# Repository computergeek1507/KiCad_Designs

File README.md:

# Copyright and Disclaimer
Copyright: Scott Hanson

This documentation describes Open Hardware and is licensed under the CERN OHL v. 1.2.

You may redistribute and modify this documentation under the terms of the CERN OHL v.1.2. (http://ohwr.org/cernohl). This documentation is distributed WITHOUT ANY EXPRESS OR IMPLIED WARRANTY, INCLUDING OF MERCHANTABILITY, SATISFACTORY QUALITY AND FITNESS FOR A PARTICULAR PURPOSE. Please see the CERN OHL v.1.2 for applicable conditions

# KiCad Designs
Repo for all my OSH KiCad PCB Designs

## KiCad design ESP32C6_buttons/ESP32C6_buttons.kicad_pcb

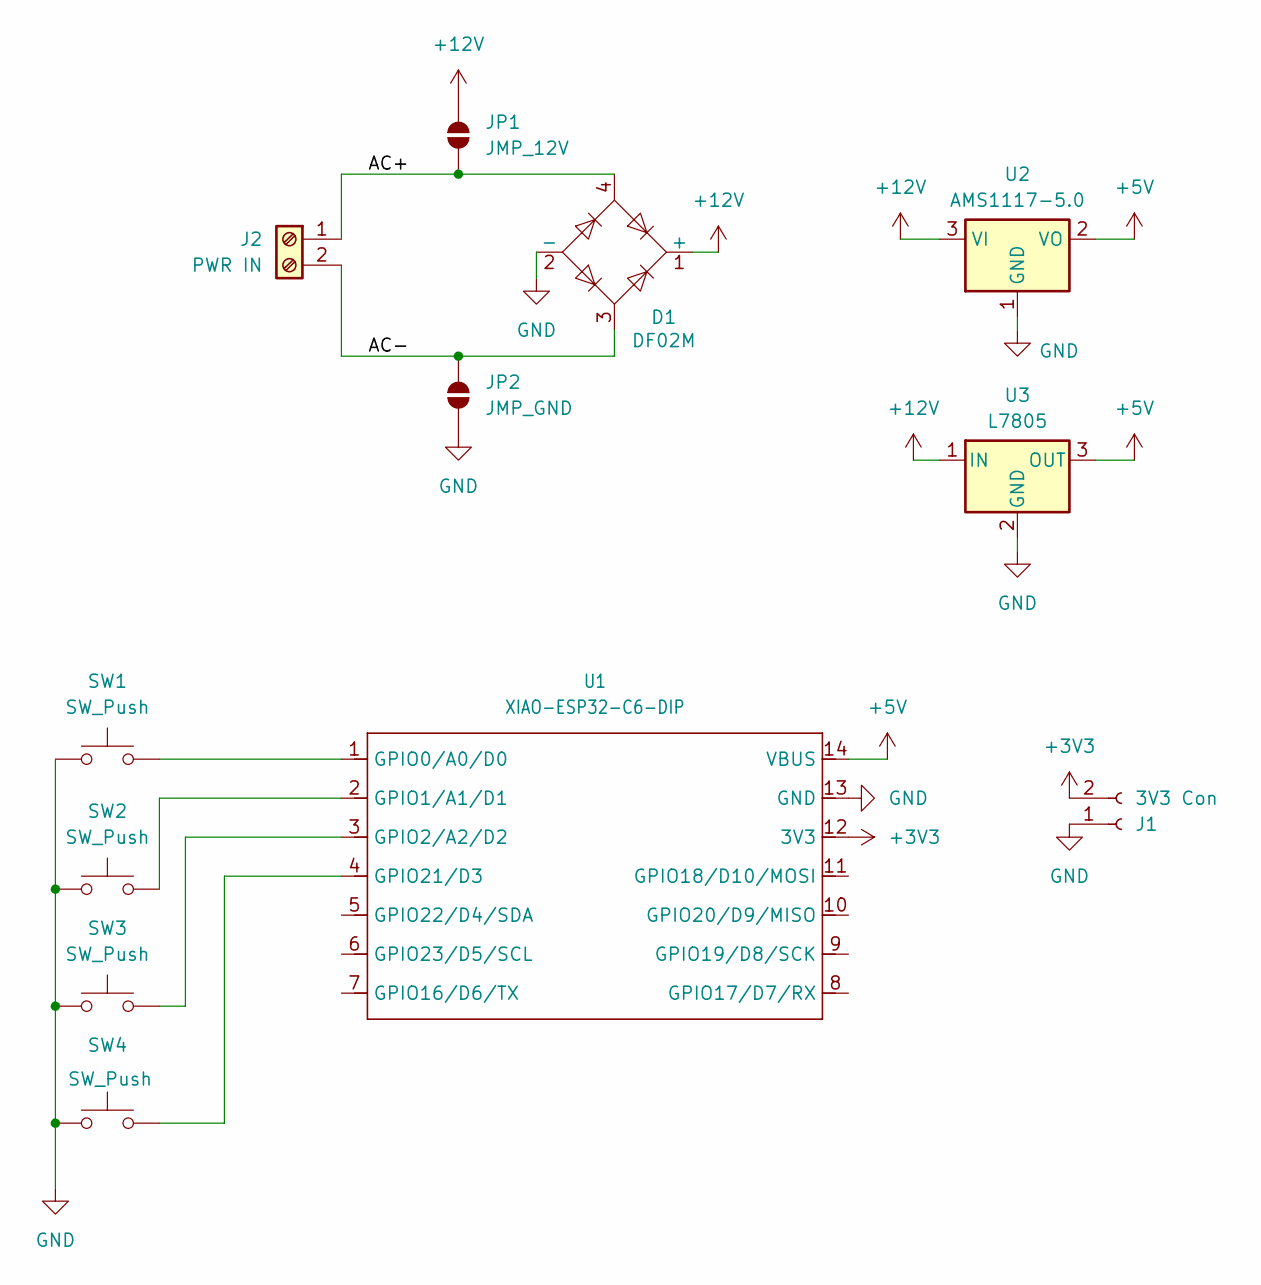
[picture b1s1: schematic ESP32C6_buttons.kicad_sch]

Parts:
D1: DF02M; Diode_Bridge_DIP-4_W7.62mm_P5.08mm
J1: 3V3 Con; JST_XH_B2B-XH-A_1x02_P2.50mm_Vertical
J2: PWR IN; PhoenixContact_MCV_1,5_2-G-5.08_1x02_P5.08mm_Vertical
JP1: JMP_12V; SolderJumper-2_P1.3mm_Open_Pad1.0x1.5mm
JP2: JMP_GND; SolderJumper-2_P1.3mm_Open_Pad1.0x1.5mm
SW1, SW2, SW3, SW4: SW_Push; SW_PUSH_6mm
U1: XIAO-ESP32-C6-DIP
U2: AMS1117-5.0; SOT-223-3_TabPin2
U3: L7805; OKI-78SR_Horz

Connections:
+3V3: J1.2, U1.12 (3V3)
+5V: U1.14 (VBUS), U2.2 (VO), U3.3 (OUT)
+12V: D1.1 (+), JP1.2 (B), U2.3 (VI), U3.1 (IN)
/AC+: D1.4, J2.1, JP1.1 (A)
/AC-: D1.3, J2.2, JP2.2 (B)
GND: D1.2 (-), J1.1, JP2.1 (A), SW1.1, SW2.1, SW3.1, SW4.1, U1.13 (GND), U2.1 (GND), U3.2 (GND)
unnamed: SW1.2, U1.1 (GPIO0/A0/D0)
unnamed: SW2.2, U1.2 (GPIO1/A1/D1)
unnamed: SW3.2, U1.3 (GPIO2/A2/D2)
unnamed: SW4.2, U1.4 (GPIO21/D3)

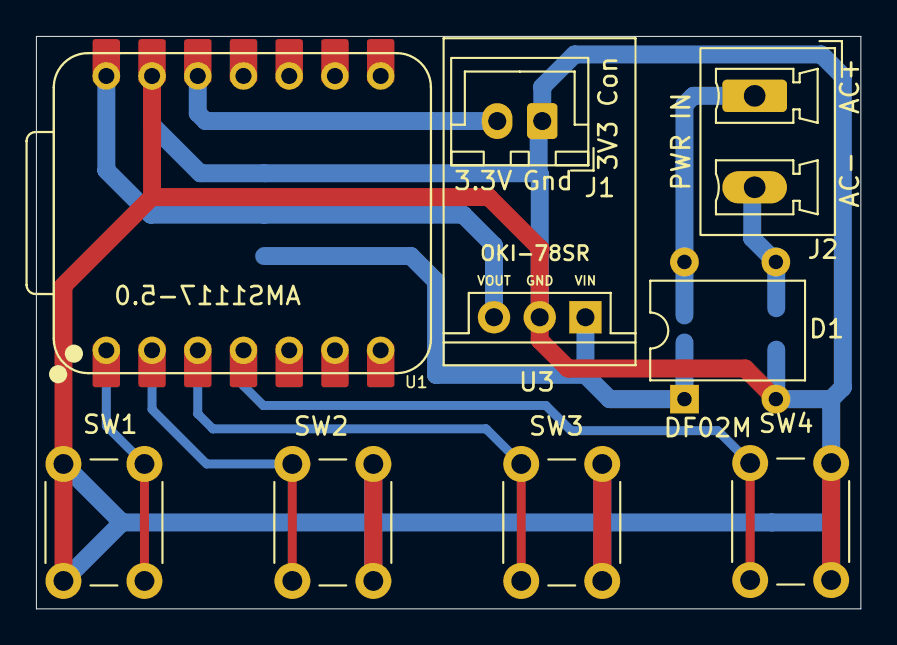
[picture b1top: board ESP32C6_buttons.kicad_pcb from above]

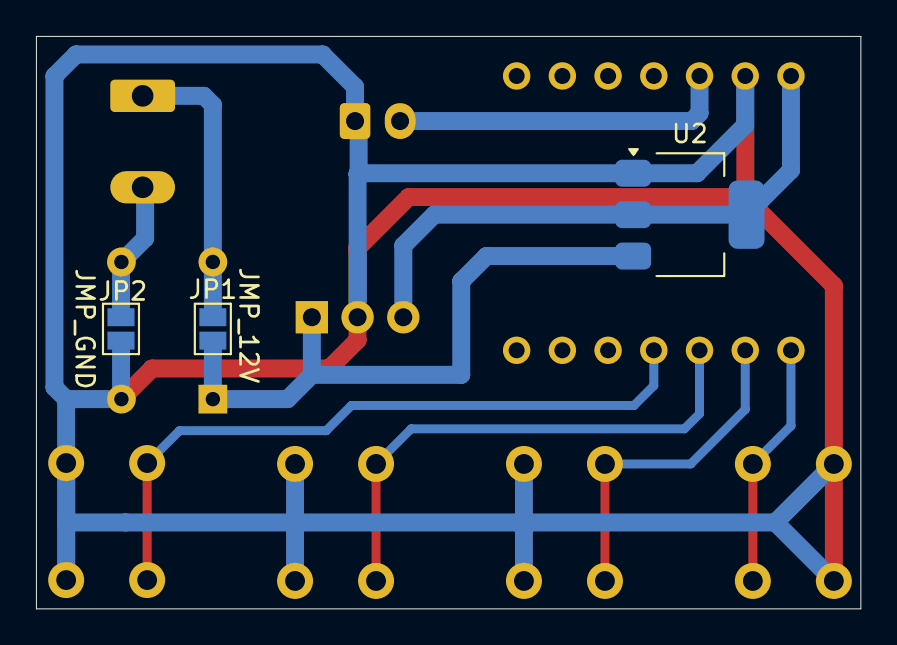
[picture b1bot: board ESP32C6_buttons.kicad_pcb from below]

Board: 2 copper layers, 45.8 x 31.8 mm, 12 parts (3 on the bottom side), 10 nets.

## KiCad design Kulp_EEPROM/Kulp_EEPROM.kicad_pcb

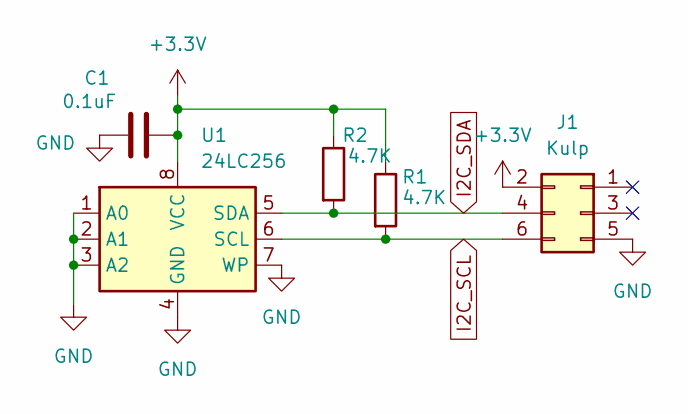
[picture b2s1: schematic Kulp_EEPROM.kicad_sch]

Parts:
C1: 0.1uF; C_0603_1608Metric_Pad1.08x0.95mm_HandSolder; MPN CL10B104KB8NNWC; LCSC C14663
J1: Kulp; 2x03_Horizontal_SMD; MPN PPTC032LFBN-RC; Digi-Key_PN S7071-ND
R1, R2: 4.7K; R_0603_1608Metric_Pad0.98x0.95mm_HandSolder; MPN RC0603JR-074K7L; LCSC C23162
U1: 24LC256; SOIC-8_3.9x4.9mm_P1.27mm; MPN 24LC256T-I/SN; Digi-Key_PN 24LC256T-I/SNCT-ND

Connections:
+3.3V: C1.1, J1.2, R1.1, R2.1, U1.8 (VCC)
GND: C1.2, J1.5, U1.1 (A0), U1.2 (A1), U1.3 (A2), U1.4 (GND), U1.7 (WP)
I2C_SCL: J1.6, R1.2, U1.6 (SCL)
I2C_SDA: J1.4, R2.2, U1.5 (SDA)

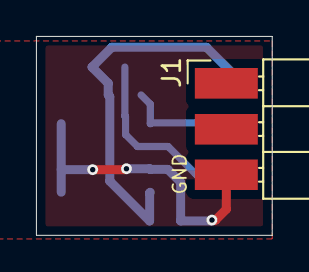
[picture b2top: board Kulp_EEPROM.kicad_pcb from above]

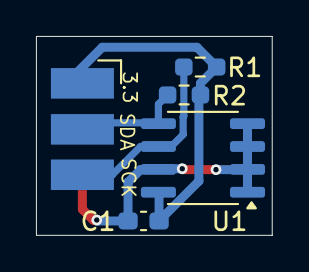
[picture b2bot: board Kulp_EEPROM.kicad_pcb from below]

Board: 2 copper layers, 13.1 x 11.0 mm, 5 parts (4 on the bottom side), 4 nets.

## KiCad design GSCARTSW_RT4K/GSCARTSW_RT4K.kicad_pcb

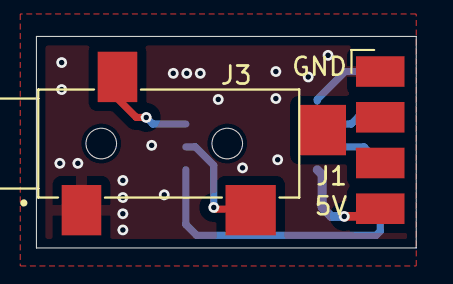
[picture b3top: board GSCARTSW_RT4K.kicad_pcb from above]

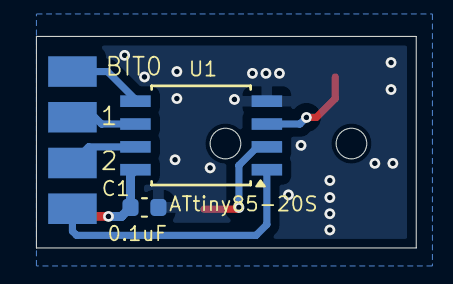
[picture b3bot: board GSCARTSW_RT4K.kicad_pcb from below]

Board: 2 copper layers, 21.1 x 11.8 mm, 4 parts (2 on the bottom side), 8 nets.

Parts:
C1: 0.1uF; C_0603_1608Metric
J1: Conn_02x04_Top_Bottom; PinSocket_2x04_P2.54mm_Horizontal_SMD
J3: SJ-3524-SMT-PI; CUI_SJ-3524-SMT-PI
U1: ATtiny85-20S; SOIC-8W_5.3x5.3mm_P1.27mm

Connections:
+5V: C1.1, J1.4, U1.8 (VCC)
GND: C1.2, J1.1, J3.1, U1.4 (GND)
IN_BIT0: J1.5, U1.5 (AREF/PB0)
IN_BIT1: J1.6, U1.6 (PB1)
IN_BIT2: J1.7, U1.7 (PB2)
RESET: J1.8, U1.1 (~RESET/PB5)
RX: J3.3, U1.3 (XTAL2/PB4)
TX: J3.2, U1.2 (XTAL1/PB3)

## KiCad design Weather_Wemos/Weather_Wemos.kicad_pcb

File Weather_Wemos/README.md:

# Copyright and Disclaimer
Copyright: Scott Hanson

This documentation describes Open Hardware and is licensed under the CERN OHL v. 1.2.

You may redistribute and modify this documentation under the terms of the CERN OHL v.1.2. (http://ohwr.org/cernohl). This documentation is distributed WITHOUT ANY EXPRESS OR IMPLIED WARRANTY, INCLUDING OF MERCHANTABILITY, SATISFACTORY QUALITY AND FITNESS FOR A PARTICULAR PURPOSE. Please see the CERN OHL v.1.2 for applicable conditions

# Weather Wemos

Breakout board for the Wemos D1 Mini to use it with the [Sparkfun Weather Meter Kit](https://www.sparkfun.com/products/15901). The design was made with all through hole components for easy assembly by most users. Open source applications were used to create this controller. [KiCad](http://kicad-pcb.org/) was used for the PCB design, and [LibreOffice](https://www.libreoffice.org/) for the documentation.

To order your own PCB upload the gerber.zip file to your favorite PCB manufacture of choice, I personally use [jlcpcb.com](https://jlcpcb.com/).

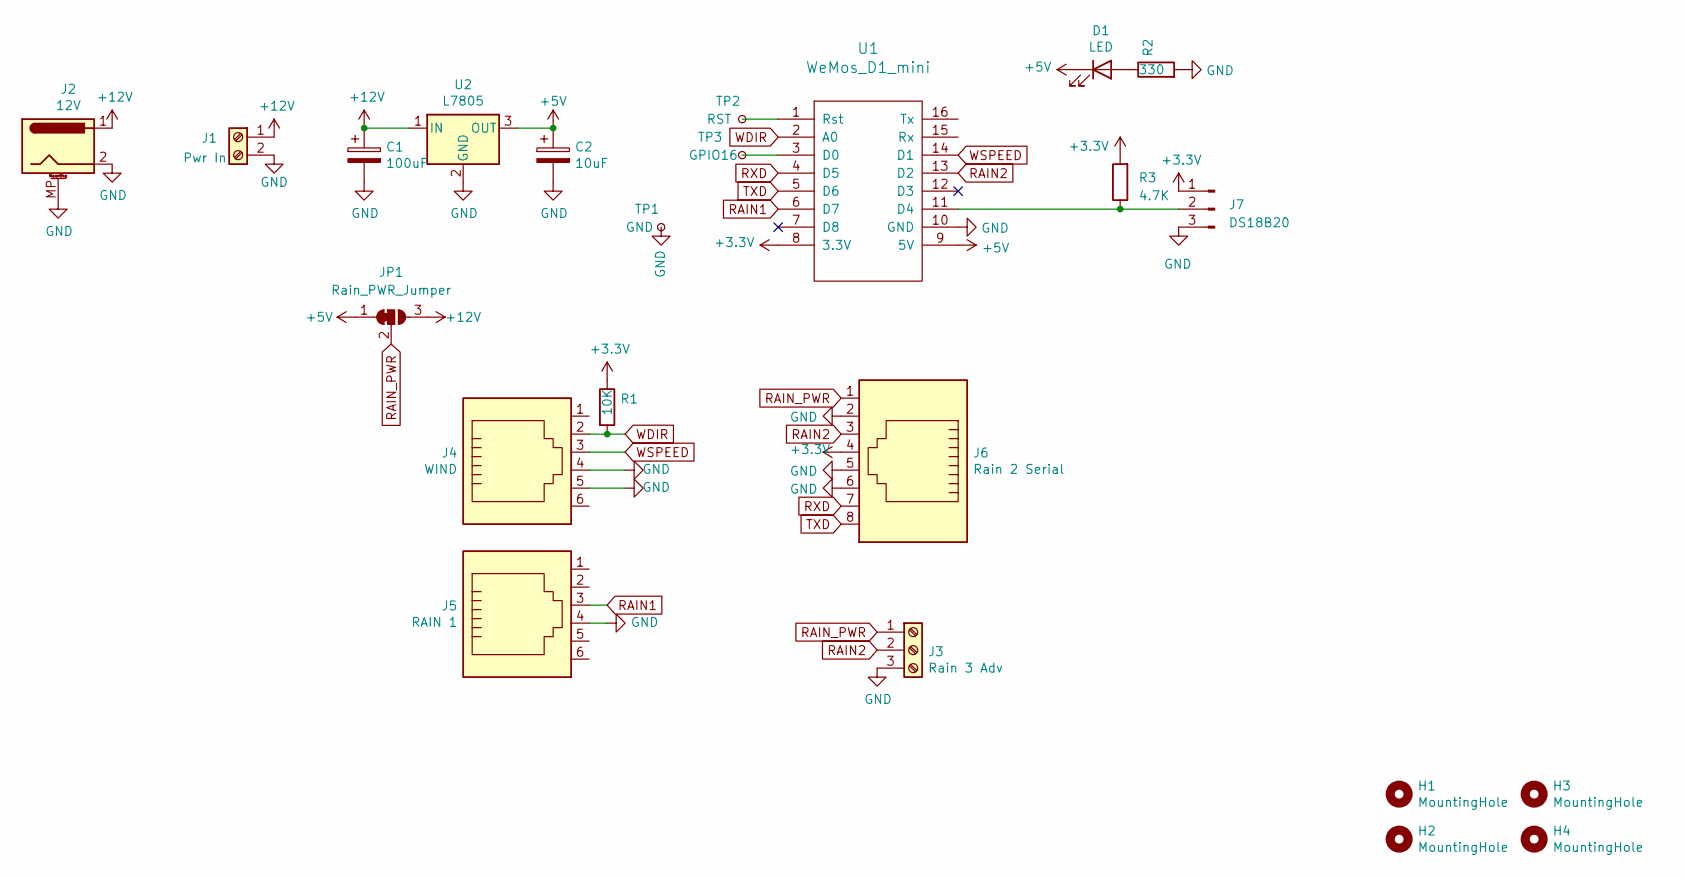
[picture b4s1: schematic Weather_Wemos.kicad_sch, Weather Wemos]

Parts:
C1: 100uF; CP_Radial_D5.0mm_P2.50mm
C2: 10uF; CP_Radial_D5.0mm_P2.50mm
D1: LED; LED_D3.0mm
H1, H2, H3, H4: MountingHole; MountingHole_3.7mm
J1: Pwr In; TerminalBlock_Phoenix_MKDS-1,5-2_1x02_P5.00mm_Horizontal
J2: 12V; BarrelJack_Horizontal
J3: Rain 3 Adv; TerminalBlock_Phoenix_MKDS-1,5-3_1x03_P5.00mm_Horizontal
J4: WIND; RJ12_Amphenol_54601; Digikey AE10391-ND
J5: RAIN 1; RJ12_Amphenol_54601; Digikey AE10391-ND
J6: Rain 2 Serial; RJ45_Amphenol_54602-x08_Horizontal
J7: DS18B20; JST_XH_B3B-XH-A_1x03_P2.50mm_Vertical
JP1: Rain_PWR_Jumper; SolderJumper-3_P1.3mm_Bridged2Bar12_RoundedPad1.0x1.5mm_Num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
R1: 10K; R_Axial_DIN0207_L6.3mm_D2.5mm_P7.62mm_Horizontal
R2: 330; R_Axial_DIN0207_L6.3mm_D2.5mm_P7.62mm_Horizontal
R3: 4.7K; R_Axial_DIN0207_L6.3mm_D2.5mm_P7.62mm_Horizontal
TP1: GND; TestPoint_Pad_1.5x1.5mm
TP2: RST; TestPoint_Pad_1.5x1.5mm
TP3: GPIO16; TestPoint_Pad_1.5x1.5mm
U1: WeMos_D1_mini; wemos-d1-mini-connectors-only
U2: L7805; TO-220-3_Vertical

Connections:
+3V3: J6.4, J7.1, R1.1, R3.2, U1.8 (3.3V)
+5V: C2.1, D1.1 (K), JP1.1 (A), U1.9 (5V), U2.3 (OUT)
+12V: C1.1, J1.1, J2.1, JP1.3 (B), U2.1 (IN)
GND: C1.2, C2.2, J1.2, J2.2, J2.MP (MountPin), J3.3, J4.4, J4.5, J5.4, J6.2, J6.5, J6.6, J7.3, R2.2, TP1.1, U1.10 (GND), U2.2 (GND)
unnamed: D1.2 (A), R2.1
unnamed: J7.2, R3.1, U1.11 (D4)
unnamed: TP3.1, U1.3 (D0)
unnamed: TP2.1, U1.1 (Rst)
RAIN1: J5.3, U1.6 (D7)
RAIN2: J3.2, J6.3, U1.13 (D2)
RAIN_PWR: J3.1, J6.1, JP1.2 (C)
RXD: J6.7, U1.4 (D5)
TXD: J6.8, U1.5 (D6)
WDIR: J4.2, R1.2, U1.2 (A0)
WSPEED: J4.3, U1.14 (D1)

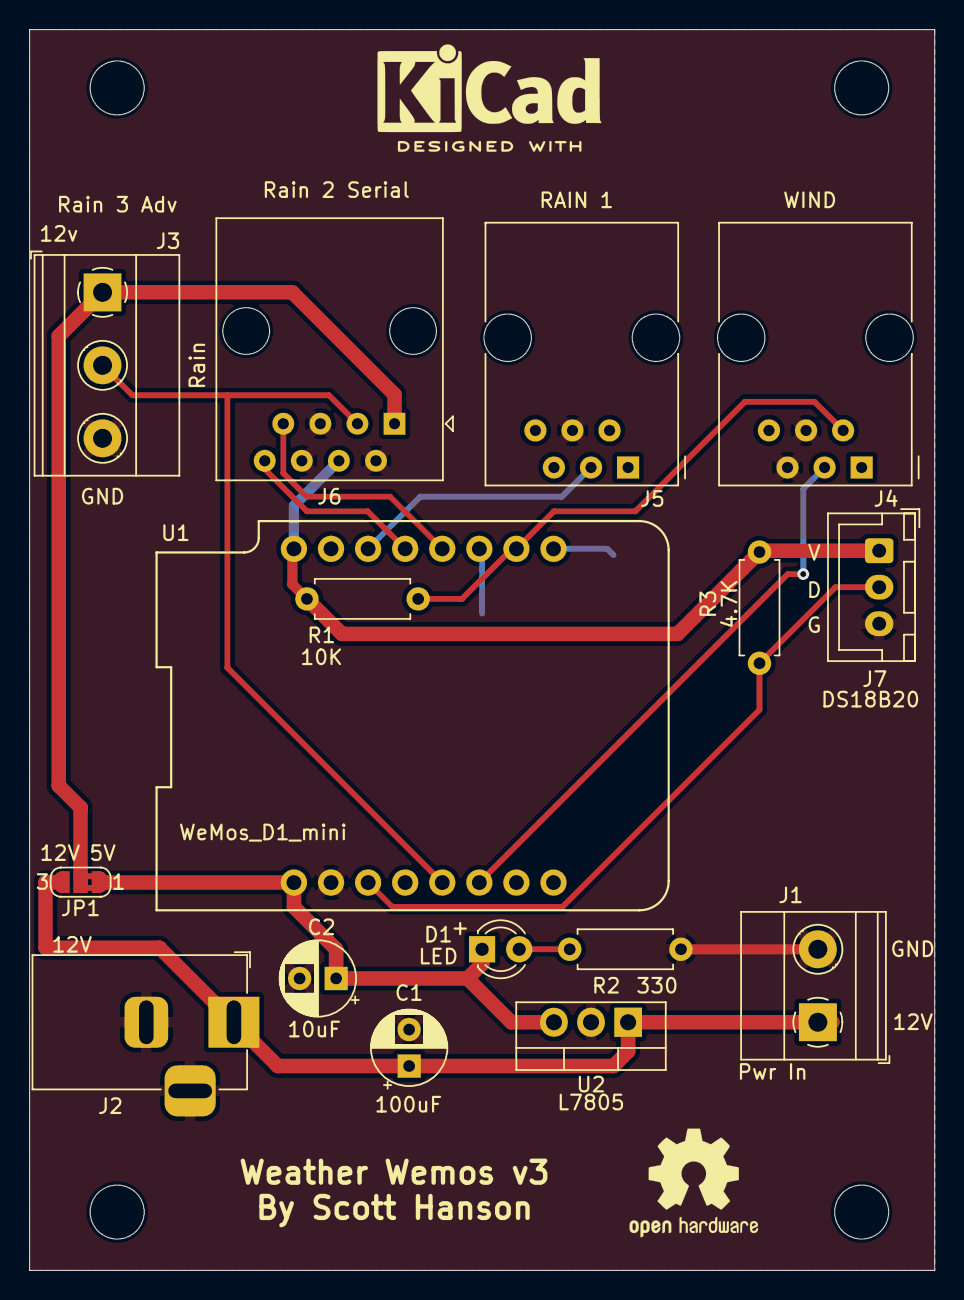
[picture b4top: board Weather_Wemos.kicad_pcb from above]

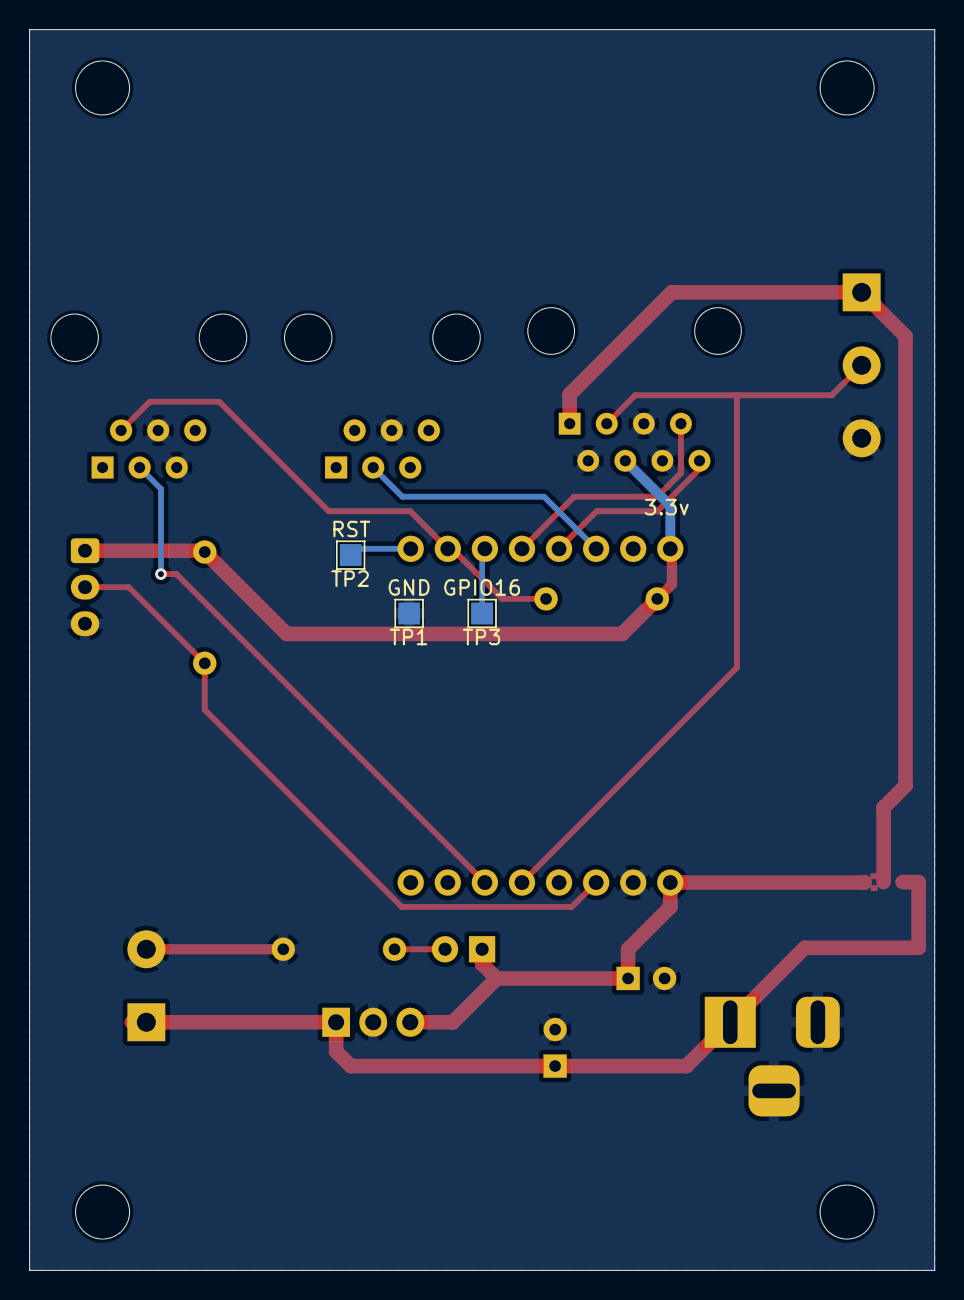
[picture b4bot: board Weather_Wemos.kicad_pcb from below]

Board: 2 copper layers, 62.0 x 85.0 mm, 23 parts (3 on the bottom side), 15 nets.

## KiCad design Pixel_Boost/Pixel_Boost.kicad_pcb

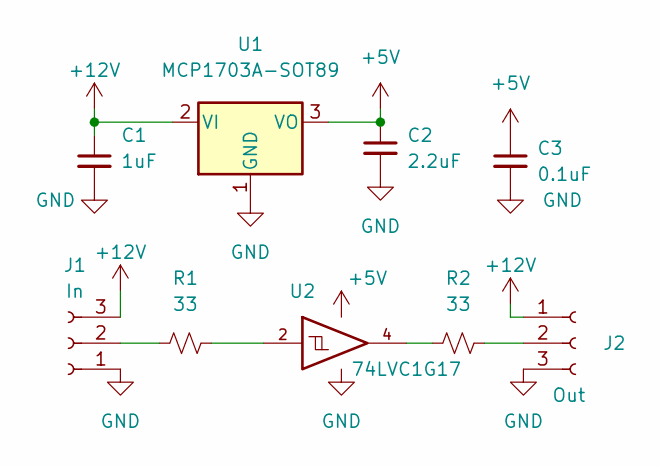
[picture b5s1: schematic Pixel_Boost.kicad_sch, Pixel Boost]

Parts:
C1: 1uF; R_0603_1608Metric; LCSC C15849
C2: 2.2uF; R_0603_1608Metric; LCSC C23630
C3: 0.1uF; R_0603_1608Metric; LCSC C14663
J1: In; PhoenixContact_MCV_1,5_3-G-3.81_1x03_P3.81mm_Vertical
J2: Out; PhoenixContact_MCV_1,5_3-G-3.81_1x03_P3.81mm_Vertical
R1, R2: 33; R_0603_1608Metric; LCSC C4184
U1: MCP1703A-SOT89; SOT-89-3; LCSC C16106
U2: 74LVC1G17; SOT-23-5; LCSC C7836

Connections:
+5V: C2.1, C3.1, U1.3 (VO), U2.5 (VCC)
+12V: C1.1, J1.3, J2.1, U1.2 (VI)
GND: C1.2, C2.2, C3.2, J1.1, J2.3, U1.1 (GND), U2.3 (GND)
unnamed: J1.2, R1.1
unnamed: J2.2, R2.2
unnamed: R1.2, U2.2
unnamed: R2.1, U2.4

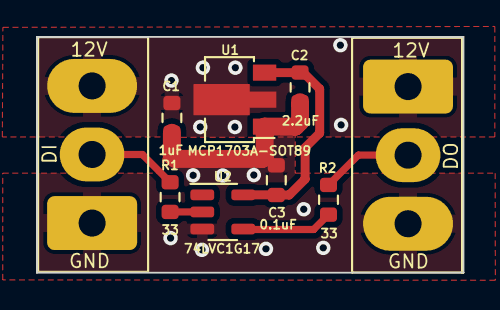
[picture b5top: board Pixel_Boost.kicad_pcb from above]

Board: 2 copper layers, 23.7 x 13.1 mm, 9 parts (0 on the bottom side), 7 nets.

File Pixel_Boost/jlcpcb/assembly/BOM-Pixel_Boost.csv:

Comment,Designator,Footprint,LCSC
0.1uF,C3,R_0603_1608Metric,C14663
1uF,C1,R_0603_1608Metric,C15849
MCP1703A,U1,SOT-89-3,C16106
2.2uF,C2,R_0603_1608Metric,C23630
33,"R1,R2",R_0603_1608Metric,C4184
74LVC1G17,U2,SOT-23-5,C840096
Out,J2,"PhoenixContact_MCV_1,5_3-G-3.81_1x03_P3.81mm_Vertical",
In,J1,"PhoenixContact_MCV_1,5_3-G-3.81_1x03_P3.81mm_Vertical",

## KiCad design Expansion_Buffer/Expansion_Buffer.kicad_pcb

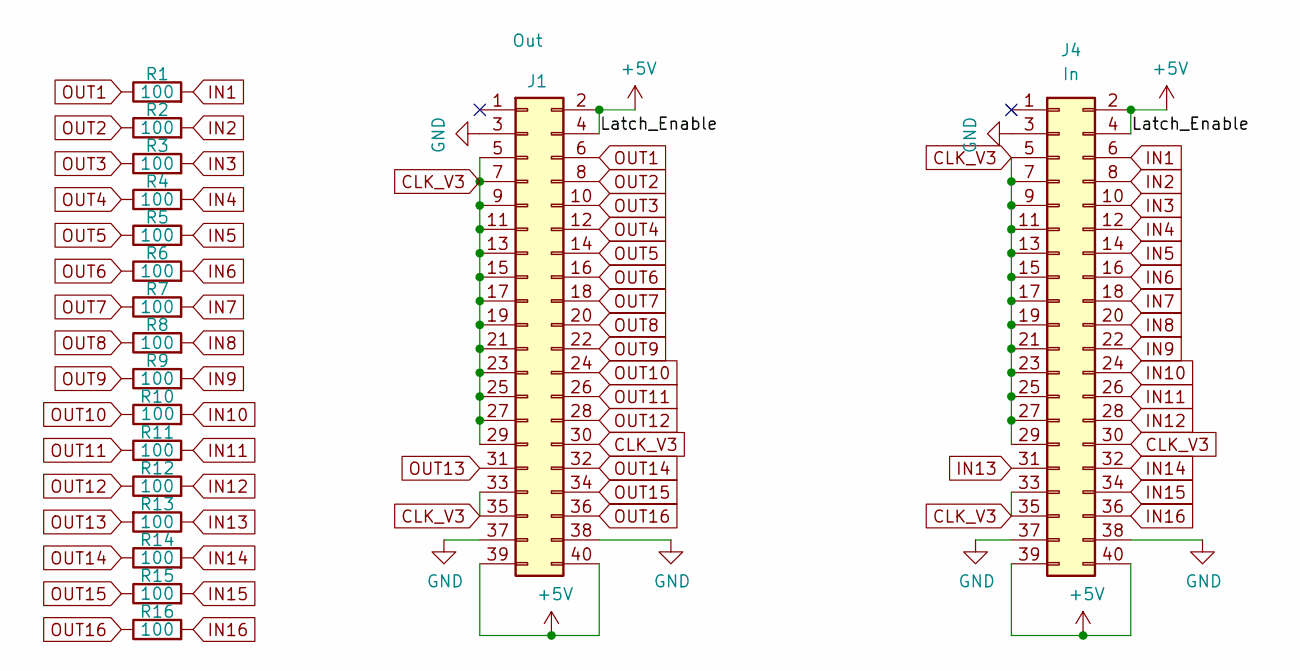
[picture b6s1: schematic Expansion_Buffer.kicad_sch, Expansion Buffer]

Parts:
J1: Out; PinSocket_2x20_P2.54mm_Vertical; MPN SBH11-PBPC-D20-ST-BK; Digi-Key_PN S9175-ND
J4: In; IDC-Header_2x20_P2.54mm_Vertical; MPN SBH11-PBPC-D20-ST-BK; Digi-Key_PN S9175-ND
R1, R2, R3, R4, R5, R6, R7, R8, R9, R10, R11, R12, R13, R14, R15, R16: 100; R_0805_2012Metric_Pad1.20x1.40mm_HandSolder

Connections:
+5V: J1.2, J1.4, J1.39, J1.40; also elsewhere on the board
CLK_V3: J1.5, J1.7, J1.9, J1.11, J1.13, J1.15, J1.17, J1.19, J1.21, J1.23, J1.25, J1.27, J1.29, J1.30, J1.33, J1.35; also elsewhere on the board
GND: J1.3, J1.37, J1.38; also elsewhere on the board
IN1: R1.2; also elsewhere on the board
IN2: R2.2; also elsewhere on the board
IN3: R3.2; also elsewhere on the board
IN4: R4.2; also elsewhere on the board
IN5: R5.2; also elsewhere on the board
IN6: R6.2; also elsewhere on the board
IN7: R7.2; also elsewhere on the board
IN8: R8.2; also elsewhere on the board
IN9: R9.2; also elsewhere on the board
IN10: R10.2; also elsewhere on the board
IN11: R11.2; also elsewhere on the board
IN12: R12.2; also elsewhere on the board
IN13: R13.1; also elsewhere on the board
IN14: R14.2; also elsewhere on the board
IN15: R15.2; also elsewhere on the board
IN16: R16.2; also elsewhere on the board
OUT1: J1.6, R1.1
OUT2: J1.8, R2.1
OUT3: J1.10, R3.1
OUT4: J1.12, R4.1
OUT5: J1.14, R5.1
OUT6: J1.16, R6.1
OUT7: J1.18, R7.1
OUT8: J1.20, R8.1
OUT9: J1.22, R9.1
OUT10: J1.24, R10.1
OUT11: J1.26, R11.1
OUT12: J1.28, R12.1
OUT13: J1.31, R13.2
OUT14: J1.32, R14.1
OUT15: J1.34, R15.1
OUT16: J1.36, R16.1

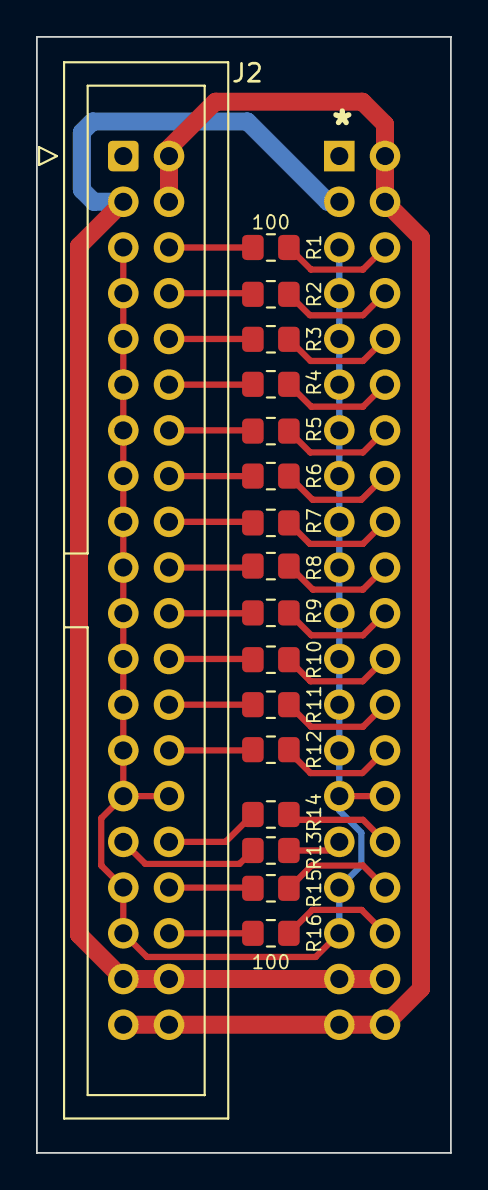
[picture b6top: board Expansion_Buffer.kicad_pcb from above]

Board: 2 copper layers, 23.0 x 62.0 mm, 18 parts (1 on the bottom side), 35 nets.

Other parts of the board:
J2: In; IDC-Header_2x20_P2.54mm_Vertical

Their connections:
+5V: J2.2, J2.4, J2.39, J2.40; also elsewhere on the board
CLK_V3: J2.5, J2.7, J2.9, J2.11, J2.13, J2.15, J2.17, J2.19, J2.21, J2.23, J2.25, J2.27, J2.29, J2.30, J2.33, J2.35; also elsewhere on the board
GND: J2.3, J2.37, J2.38; also elsewhere on the board
IN1: J2.6; also elsewhere on the board
IN2: J2.8; also elsewhere on the board
IN3: J2.10; also elsewhere on the board
IN4: J2.12; also elsewhere on the board
IN5: J2.14; also elsewhere on the board
IN6: J2.16; also elsewhere on the board
IN7: J2.18; also elsewhere on the board
IN8: J2.20; also elsewhere on the board
IN9: J2.22; also elsewhere on the board
IN10: J2.24; also elsewhere on the board
IN11: J2.26; also elsewhere on the board
IN12: J2.28; also elsewhere on the board
IN13: J2.31; also elsewhere on the board
IN14: J2.32; also elsewhere on the board
IN15: J2.34; also elsewhere on the board
IN16: J2.36; also elsewhere on the board

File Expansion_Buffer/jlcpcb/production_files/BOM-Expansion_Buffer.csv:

Comment,Designator,Footprint,LCSC
100,"R1,R10,R11,R12,R13,R14,R15,R16,R2,R3,R4,R5,R6,R7,R8,R9",R_0805_2012Metric_Pad1.20x1.40mm_HandSolder,C17408
In,J2,IDC-Header_2x20_P2.54mm_Vertical,C9138

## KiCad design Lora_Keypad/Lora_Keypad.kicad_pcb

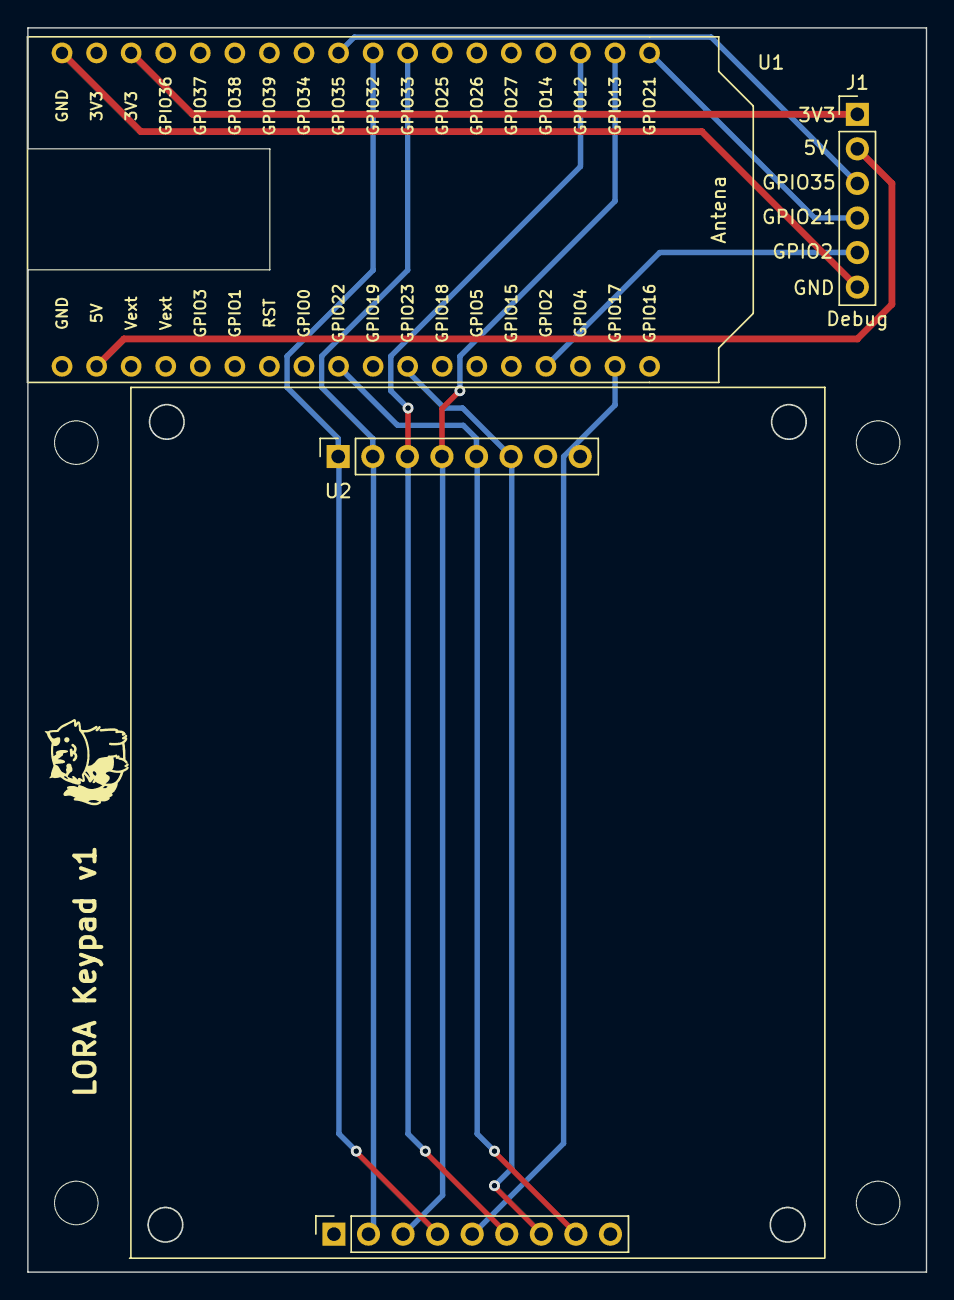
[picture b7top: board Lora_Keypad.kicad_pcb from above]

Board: 2 copper layers, 66.0 x 91.4 mm, 7 parts (0 on the bottom side), 13 nets.

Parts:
H1, H2, H3, H4: MountingHole; MountingHole_3.2mm_M3
J1: Debug; PinHeader_1x06_P2.54mm_Vertical
U1: Heltec_Wifi_LoRa_V1; Heltec_WiFi_LoRa_V2
U2: 3x4_keypad

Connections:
+3.3V: J1.1, U1.34 (3V3)
+5V: J1.2, U1.2 (5V)
C1: U1.27 (LORA_DIO2/XTAL32/TOUCH9/ADC1_4/GPIO32), U2.A1 (C1), U2.B4 (C1)
C2: U1.26 (LORA_DIO1/XTAL32/TOUCH8/ADC1_5/GPIO33), U2.A2 (C2), U2.B2 (C2)
C3: U1.21 (TOUCH5/ADC2_5/GPIO12), U2.A3 (C3), U2.B6 (C3)
GND: J1.6, U1.36 (GND)
unnamed: J1.3, U1.28 (ADC1_7/GPIO35)
unnamed: J1.4, U1.19 (V_SPI_HD/SDA/GPIO21)
unnamed: J1.5, U1.15 (TOUCH2/HSPI_WP/ADC2_2/GPIO2)
R1: U1.20 (TOUCH4/ADC2_4/GPIO13), U2.A4 (R1), U2.B3 (R1)
R2: U1.9 (U0_RTS/V_SPI_WP/SCL/GPIO22), U2.A5 (R2), U2.B8 (R2)
R3: U1.11 (V_SPI_D/GPIO23), U2.A6 (R3), U2.B7 (R3)
R4: U1.17 (U2_TX/GPIO17), U2.A7 (R4), U2.B5 (R4)

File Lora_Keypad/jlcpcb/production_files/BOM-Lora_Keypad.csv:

Comment,Designator,Footprint,LCSC
~,U2,3x4_keypad,
Heltec_Wifi_LoRa_V1,U1,Heltec_WiFi_LoRa_V2,
Debug,J1,PinHeader_1x06_P2.54mm_Vertical,

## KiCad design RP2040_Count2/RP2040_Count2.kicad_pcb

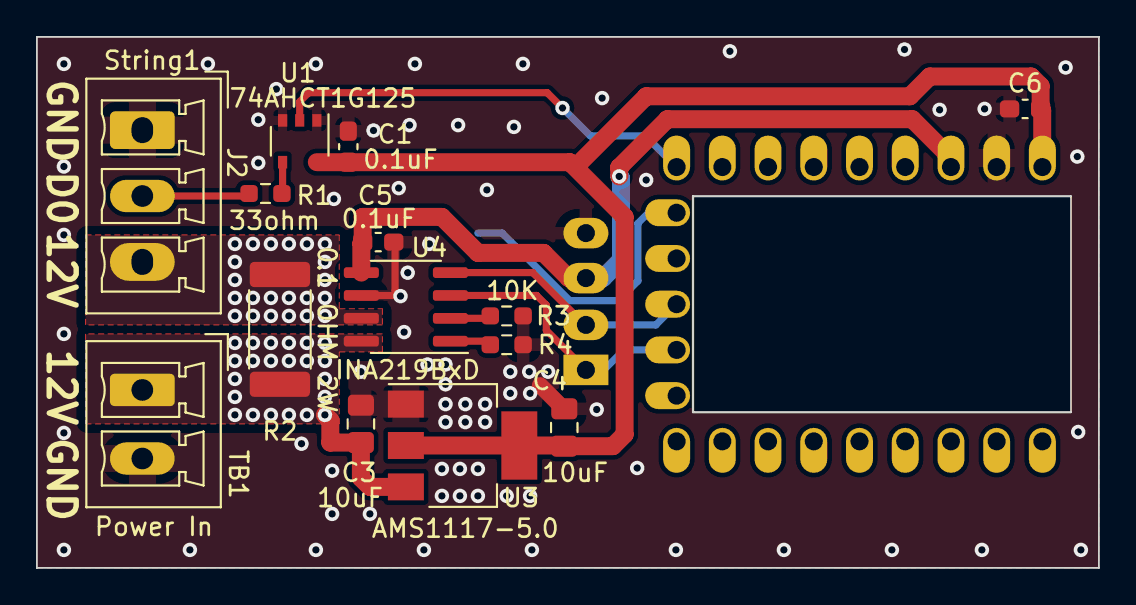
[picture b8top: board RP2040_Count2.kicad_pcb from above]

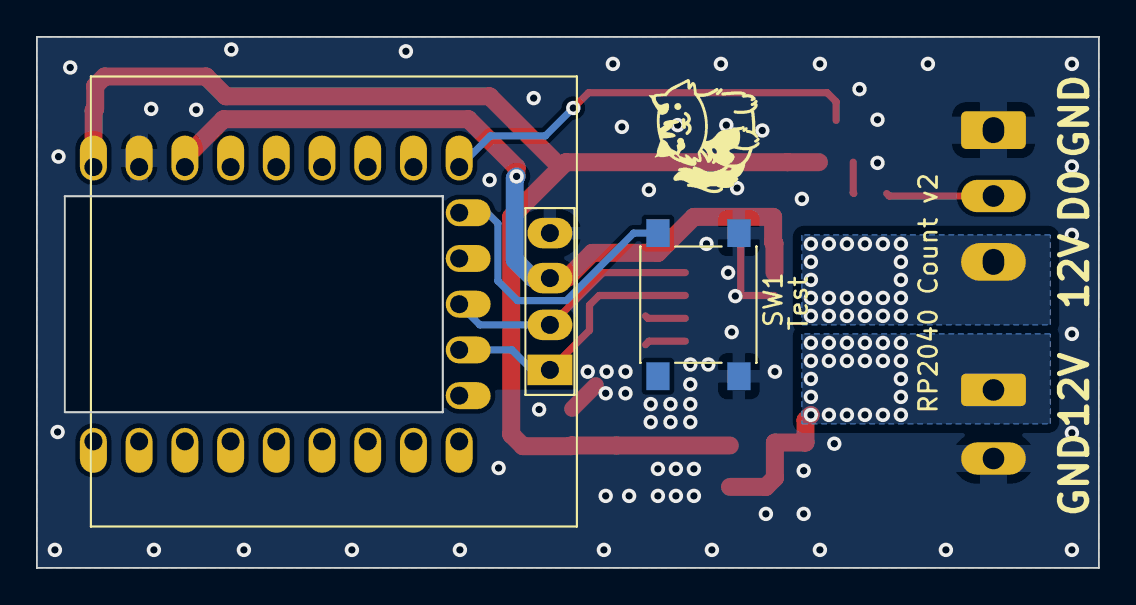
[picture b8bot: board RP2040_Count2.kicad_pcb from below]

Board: 2 copper layers, 59.0 x 29.5 mm, 17 parts (2 on the bottom side), 13 nets.

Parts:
C1, C5, C6: 0.1uF; C_0603_1608Metric_Pad1.08x0.95mm_HandSolder
C3, C4: 10uF; C_0805_2012Metric_Pad1.18x1.45mm_HandSolder
J2: String1; PhoenixContact_MCV_3.81mm_3.5mm_1x03_Vertical
J3: OLED; OLED-SSD1306-128X64-I2C-THT_SCOTT2
R1: 33ohm; R_0603_1608Metric_Pad0.98x0.95mm_HandSolder
R2: 0.1 OHM 2W; R_2512_6332Metric_Pad1.40x3.35mm_HandSolder
R3, R4: 10K; R_0603_1608Metric_Pad0.98x0.95mm_HandSolder
SW1: Test; SW_Push_1P1T_NO_6x6mm_H9.5mm
TB1: Power In; PhoenixContact_MCV_1,5_2-G-3.81_1x02_P3.81mm_Vertical
U1: 74AHCT1G125; TSOP-5_1.65x3.05mm_P0.95mm
U2: rp2040-zero; rp2040-zero-tht
U3: AMS1117-5.0; SOT-223-3_TabPin2
U4: INA219BxD; SOIC-8_3.9x4.9mm_P1.27mm

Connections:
+3.3V: C5.1, J3.3, U2.21 (3V3), U4.5 (VS)
+5V: C1.1, C4.1, C6.2, U1.5 (VCC), U2.23 (5V), U3.2 (VO)
/DOUT1: J2.2, R1.1
GND: C1.2, C3.2, C4.2, C5.2, C6.1, J2.1, J3.4, R3.2, R4.2, SW1.2, TB1.2, U1.1, U1.3 (GND), U2.22 (GND), U3.1 (GND), U4.6 (GND)
I2C_SCL: J3.2, U2.12 (11), U4.4 (SCL)
I2C_SDA: J3.1, U2.11 (10), U4.3 (SDA)
unnamed: R1.2, U1.4
unnamed: R3.1, U4.2 (A0)
unnamed: R4.1, U4.1 (A1)
OUT1: U1.2, U2.15 (14)
SW1: SW1.1, U2.14 (13)
VIN1: C3.1, R2.1, TB1.1, U3.3 (VI), U4.8 (IN+)
VOUT1: J2.3, R2.2, U4.7 (IN-)

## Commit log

2020-03-04 added license
2020-03-04 Added HP power breakout
2020-03-05 added README.md
2020-03-05 added pic
2020-03-06 added silkscreen with board information
2020-03-13 made the PCB a little smaller
2020-03-13 added Manufacturer PNs
2020-03-14 added fused breakout
2020-04-12 Added ESP Doorbell
2020-04-12 Added ESP Switch
2020-06-15 added wemo shield
2020-07-12 added more text to silkscreen
2020-09-01 added PiHat
2020-09-02 added drill files
2020-09-19 added BOM and Added serial port silkscreen
2020-09-19 added readme
2020-09-19 trying to fix the bom path
2020-09-19 added sockets to BOM
2020-09-26 added PiOled
2020-09-26 reflood gnd
2020-11-07 added Receiver Converter
2020-11-07 rotated connectors
2020-11-22 added schematic
2021-01-18 Update PiHat_BOM.ods
    Corrected swapped Digi-Key part numbers to correct column for some components.
2021-02-24 make the holes a little bigger
2021-03-07 added Power Distribution
2021-03-07 added title
2021-03-11 Update Silkscreen and Added BOM
2021-03-29 added power distros
2021-03-29 fix readmes
2021-05-13 added ESP32 Controllers
2021-05-13 added 3d models
2021-05-13 added new gerbers
2021-06-03 added fpp to flex adapter
2021-07-03 Added Weather Breakout
2021-07-06 added PDF schematic and Updated Project name in files
2021-08-28 added 3 to 4
2021-08-28 Created BOM
2021-08-29 minor update
2021-09-04 added 3.3v jumper
2021-09-07 swapped header
2021-09-07 working on Lolin Pro 32 Controller
2021-09-12 added gerbers
2021-09-17 added readme and picture
2021-09-17 remove wrong link
2021-09-17 Added Pic and readme
2021-09-24 added OLED
2021-09-30 remove through hole wording
2021-11-04 Added PI Zero Breakout
2021-11-07 added ESP32-CAM board
2021-11-07 some fixes
2021-11-07 added kicad logo
2022-02-10 added header lib
2022-02-11 changed pinout to match FPP and added Expansion port
2022-02-11 remove nightly
2022-02-11 added iBom
2022-05-02 working on Power Distro PCB
2022-05-02 Generated Gerbers
2022-05-06 upgraded to 6, changed pinout
2022-12-10 added
2022-12-12 added booster
2022-12-13 added logo
2023-01-11 added esp32 shift register controller
2023-02-20 added pico weather
2023-02-23 update to add EDM RDS header
2023-02-23 removed old files
2023-02-26 added temperature headers
2023-02-26 added temperature sensor
2023-03-12 added dmx to stepper
2023-03-12 Added untested Firmware and LCSC partnumbers
2023-03-12 added lcsc pns
2023-03-21 redo PCB layout, Add servo headers and opocouplers to limit switches
2023-03-26 added Optocoupler to limits switches
2023-03-26 fix R3
2023-04-10 fix RJ45 LCSC PN
2023-05-31 added console breakout
2023-05-31 added digikey part numbers
2023-07-03 added WT32-ETH01 board
2023-08-30 added keypad
2023-09-01 added debug header
2023-09-01 added mounting wholes
2023-10-30 added new pixel boost
2023-10-30 change footprint
2023-11-07 added buffer
2024-01-19 minor fixes
2024-02-03 added 3D model
2024-02-03 added jlc
2024-02-11 switch to RP2040
2024-02-11 remove nonworking
2024-03-14 added more leds
2024-03-14 fix JLC rotation of LEDs
2024-03-14 fix bom name
2024-03-15 move header
2024-03-21 fix leds
2025-07-04 add plug in 3 to 4 adapter
2025-07-04 retrotink 4k serial adapter
2025-07-04 backup kulp eeprom
2026-04-10 add button board
2026-04-19 add buttons
2026-05-04 update to add rectifier
